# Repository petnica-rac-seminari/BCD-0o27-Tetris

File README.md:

CHECK THE DOCUMENTATION FOLDER FOR INFORMATION ABOUT THE HARDWARE AND HOW TO BUILD IT.

The BalcCon Cyberdeck 0o27 (BCD-0o27) comes with a development framework that makes it easier to add functionality to the cyberdeck. This development guide introduces the framework, advises coding best practices and provides examples for adding functionality to the BCD.
Of course, you can ignore all of that and program the BCD either with esp-idf, rust, or any other framework that allows you to program ESP32 chips directly. However, this is not covered in this guideline.

# Introduction to the BCD-0o27 Framework
Before reading this chapter it is advisable to get  a local copy of the framework (see [[#Getting the Framework]]) and set up the development environment (see [[#Setting up the Development Toolchain]]). 
The framework consists of the following components:
- **Drivers**: The drivers for the hardware, namely the ST7735 display, the WS2812 LEDs  and the input buttons (aka controller) as well as the serial console. (Sometimes, drivers and libraries are not distinguished)
- **Libraries**: Libraries are provided for common tasks like opening a console on the serial port, establishing ssl connections or displaying graphical elements.
- **Modules**: Modules are programs that can be launched by the user. They can be simplest demo applications or complex programs.
- **Console Commands**: Console commands are programs that can be launched from the console. As modules, console commands can have any level of complexity. While usually they mainly interact with the serial console, they may - just as modules - access other hardware as well.

This document is currently being developed. For the time being, it is recommended to check the appendix to clone the repository. Then use the example firmware provided in the directory.

> [!info]
> You can connect to the badge using a serial console and a usb-c data cable. Make sure you use a terminal that understands ansi sequences. You can use the integrated serial monitor of platformio or espressif, but its highly recommended to use syncterm or minicom.

> [!warning]
> There currently is a bug in the serial console that will not give you a prompt when you connect using a serial terminal. In that case, leave the connection open and simply reset the badge by pushing the reset button - left button under the display.

# Appendix
## Getting the Framework
The framework is hosted as a git repository at https://gitlab.com/fschuetz/bcd-0o27.git. The repository makes heavy use of submodules, as many components for the BCD-0o27 are developed in parallel.
To create a local repository using git follow these steps:
```bash
git clone --recurse-submodules https://gitlab.com/fschuetz/bcd-0o27
```

## Setting up the Development Toolchain
In this chapter we will show how to set up the development environment consisting of git, espidf, Microsoft Visual Studio Code and Plattformio. If you are an experienced user, feel free to use the IDE of your choice.
### Installing GIT and cloning the repository
We will use git from the command line, as we have to deal with submodules, which are not well supported in the Visual Studio Code IDE.
If you have git already installed, you can skip this step.
1. Install git for your platform. Follow the guide at [Gitlab](https://docs.gitlab.com/ee/topics/git/how_to_install_git/)
2. Clone the repository: 
    ```bash
    git clone --recurse-submodules https://gitlab.com/fschuetz/bcd-0o27
    ```
Some tips on working with submodules, in case you run into a head detached situation: https://stackoverflow.com/questions/18770545/why-is-my-git-submodule-head-detached-from-master

### Install Microsoft Visual Studio Code (VSCode)
1. Install [VSCode](https://code.visualstudio.com/) for your operating system.
2. Open VSCode.

### Install C/C++ and PlatformIO Extensions
1. In VSCode: Open the "Extensions" side bar on the left side.
2. Search for the "C/C++" extension by Mircrosoft and install it.
3. Search for the PlatformIO IDE by PlatformIO and install it. See [PlatformIO IDE for VSCode](https://docs.platformio.org/en/latest/integration/ide/vscode.html#ide-vscode)
4. Once installation has finished, restart VSCode

### Build and Upload the Firmware 
In this chapter we will build the filesystem image and the firmware and upload both to the badge. If this works, then you can start developing your own firmware using the framework. For testing we highly recommend, taking the example in the directory `firmware/example` rather than the framework, as the example will give you running firmware that allows you to see something actually happening.
1. Start Microsoft Visual Studio and make sure you are in a new window, with no project loaded.
2. Select the alien head in the left bar (Platformio menu)
3. A left band appears. Select the blue button "Pick a folder"
4. From the cloned repository choose the `firmware/example` or the `firmware/framework` folder (as written above, its recommended to start with the example rather than the plain framework).
5. Click open.
6. Wait for platformio to configure itself. This is IMPORTANT: Between now and building the file there might raise popups in the bottom left corner asking you to install extensions or configurations. Usually you are asked to intall C++ specific extensions and CMake specific extensions. Confirm all of them. For CMake, if asked, you can "scan for kits". Scan for kits may also go away on itself, then everything is fine as well. 
7. If all went well so far you will recognise a blue ribbon / button on the bottom and some symbols like a home, a checkmark, roght pointing arrow etc.. If there is the message "Platformio: Loading tasks..." wait until it disapears. (this may take a long while). PlatformIO will automatically configure the project.
8. Open the file main.cpp in the "src" folder.
9. In the bottom task list (with the blue ribbon / button and the checkmark etc...), first choose the build environment by clicking on the symbol that looks like a folder and says "Switch Platformio Project Environment" if you hover over it. Usually it reads default right to the symbol. Choose `env:BCD-0o27-5KY` (or the `env:BCD-0o27-5KY-release` if you want to build for release rather than debug - if unsure make a debug build).
10. Now select the checkmark to build the project. This builds the project. Dependencies are pulled in automatically. In case Platformio does not pull in the Espressif 32 framework, follow the steps in the note below to install it manually.
11. If the project builds successfully, connect your badge to the computer using a usb-c cable (make sure it is actually a data cable and not just a charging cable)
12. Make sure the device is recognised. If the device is not recognised and a com port assigned, you might have to install a driver for the CH340 serial bridge. Follow the instructions from [Sparkfun](https://learn.sparkfun.com/tutorials/how-to-install-ch340-drivers/all#drivers-if-you-need-them)
13. Once the device is recognised, in VSCode we will build the file system image, upload it and then upload the code.
14. From the side bar choose the PlatformIO icon (alien head)
15. Select BCD-0o27 -> Plattform -> Build Filesystem Image
16. When finished, select BCD-0o27 -> Platform -> Upload Filesystem Image (BCD-0o27)
17. When finished, select the right pointing arrow ("Platformio: Upload") in the blue ribbon at the bottom. The project will be built and uploaded to the badge.
18. Either launch the serial console from the blue ribbon by selecting the plug icon ("Platformio: Serial Monitor") or use minicom (preferred). Note, that the Platformio Serial Monitor may display some strange characters or double print the prompt as it does not fully support the output mode. IMPORTANT: Due to a bug, the serial console only works for input if the connection was made at badge startup. If you do not see a prompt, leave the console on and restart the badge by pushing the power button (left between display and battery holder).
19. CRITICAL: Make sure, that you DO NOT have a serial monitor running when trying to flash the badge. This will lead to flash failure (for both, filesystem and firmware).

Note: The Espressif 32 framework should install automatically when building the project. If this is not the case, you can install it manually:
1. Open the Platformio sidebar (left side, alien head icon).
2. Select PIO Home -> Platforms
3. Click on the "Embedded" tab. Search for "Espressif 32" and click it.
4. Install the latest version. (At the time of writing this is version 5.1.0. While we plan to adapt the framework to newer versions, you might want to select this version if the newest version is not working due to breaking changes.)
5. Once the installation has completed confirm the success dialog.
### Helpful Resources
[Espressif 32 for Platformio](https://docs.platformio.org/en/latest/platforms/espressif32.html)

## Misc notes - ignore please
### Updating mirrors 
Go to lib directory of mirror
```
git fetch upstream 
git merge upstream/master
git push
```

### Updating submodules
```
git fetch
git pull
```

# Coding Style
```c++
ESP_LOGE(TAG_MODULE_NAME, "This is a rather long error message."
		"It should be spred on two lines");
```
If functions too long, spread on multiple lines. Two lines, indent second line by one tab and finish the line with closing bracket and ;. If more than two lines use one argument per line and close on a separate line as follows:
```c++
myfunction_with_many_arguments(
	argument 1,
	argument 2,
	argument 3

```

TO BE CONTINUED

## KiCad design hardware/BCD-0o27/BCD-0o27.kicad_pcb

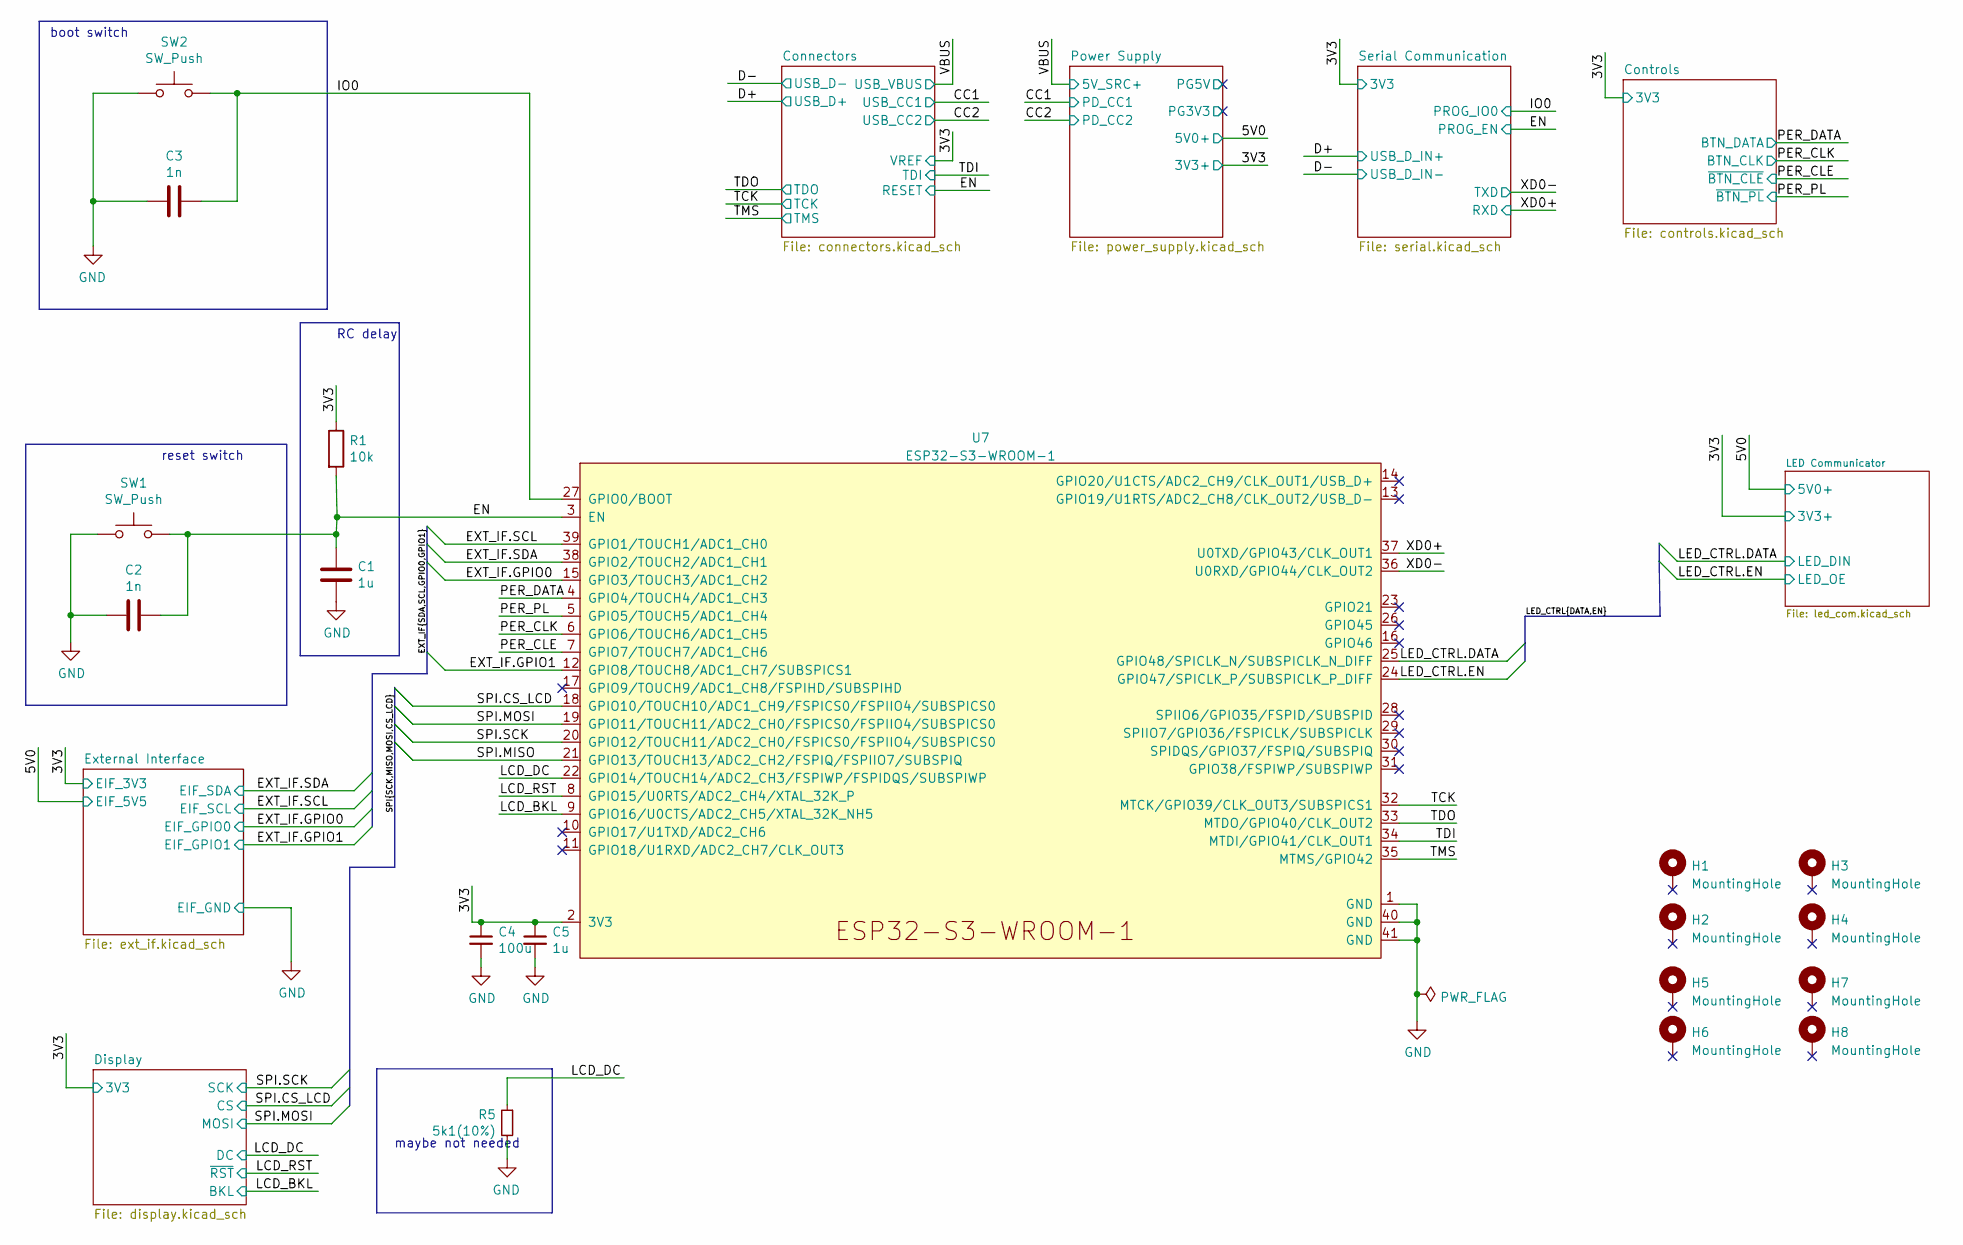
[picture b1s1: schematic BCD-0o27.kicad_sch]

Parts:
C1, C5: 1u; C_0805_2012Metric; LCSC C28323
C2, C3: 1n; C_0805_2012Metric; LCSC C46653
C4: 100u; C_1206_3216Metric; LCSC C15008
H1, H2, H3, H4, H5, H6, H7, H8: MountingHole; MountingHole_2.2mm_M2_ISO7380_Pad_TopBottom
R1: 10k; R_0805_2012Metric; LCSC C17414
R5: 5k1(10%); R_0603_1608Metric; LCSC C23186
SW1, SW2: SW_Push; XUNPU TS-1087S Tactile Switch; LCSC C455268
U7: ESP32-S3-WROOM-1; LCSC C2913202

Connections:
/3V3: C4.1, C5.1, R1.1, U7.2 (3V3); also elsewhere on the board
/EN: C1.1, C2.1, R1.2, SW1.2, U7.3 (EN); also elsewhere on the board
/EXT_IF.GPIO0: U7.15 (GPIO3/TOUCH3/ADC1_CH2); also elsewhere on the board
/EXT_IF.GPIO1: U7.12 (GPIO8/TOUCH8/ADC1_CH7/SUBSPICS1); also elsewhere on the board
/EXT_IF.SCL: U7.39 (GPIO1/TOUCH1/ADC1_CH0); also elsewhere on the board
/EXT_IF.SDA: U7.38 (GPIO2/TOUCH2/ADC1_CH1); also elsewhere on the board
/IO0: C3.1, SW2.1, U7.27 (GPIO0/BOOT); also elsewhere on the board
/LCD_BKL: U7.9 (GPIO16/U0CTS/ADC2_CH5/XTAL_32K_NH5); also elsewhere on the board
/LCD_DC: R5.1, U7.22 (GPIO14/TOUCH14/ADC2_CH3/FSPIWP/FSPIDQS/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); also elsewhere on the board
/LCD_RST: U7.8 (GPIO15/U0RTS/ADC2_CH4/XTAL_32K_P); also elsewhere on the board
/LED_CTRL.DATA: U7.25 (GPIO48/SPICLK_N/SUBSPICLK_N_DIFF); also elsewhere on the board
/LED_CTRL.EN: U7.24 (GPIO47/SPICLK_P/SUBSPICLK_P_DIFF); also elsewhere on the board
/PER_CLE: U7.7 (GPIO7/TOUCH7/ADC1_CH6); also elsewhere on the board
/PER_CLK: U7.6 (GPIO6/TOUCH6/ADC1_CH5); also elsewhere on the board
/PER_DATA: U7.4 (GPIO4/TOUCH4/ADC1_CH3); also elsewhere on the board
/PER_PL: U7.5 (GPIO5/TOUCH5/ADC1_CH4); also elsewhere on the board
/SPI.CS_LCD: U7.18 (GPIO10/TOUCH10/ADC1_CH9/FSPICS0/FSPIIO4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); also elsewhere on the board
/SPI.MISO: U7.21 (GPIO13/TOUCH13/ADC2_CH2/FSPIQ/FSPIIO7/S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)
/SPI.MOSI: U7.19 (GPIO11/TOUCH11/ADC2_CH0/FSPICS0/FSPIIO4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); also elsewhere on the board
/SPI.SCK: U7.20 (GPIO12/TOUCH11/ADC2_CH0/FSPICS0/FSPIIO4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); also elsewhere on the board
/TCK: U7.32 (MTCK/GPIO39/CLK_OUT3/SUBSPICS1); also elsewhere on the board
/TDI: U7.34 (MTDI/GPIO41/CLK_OUT1); also elsewhere on the board
/TDO: U7.33 (MTDO/GPIO40/CLK_OUT2); also elsewhere on the board
/TMS: U7.35 (MTMS/GPIO42); also elsewhere on the board
/XD0+: U7.37 (U0TXD/GPIO43/CLK_OUT1); also elsewhere on the board
/XD0-: U7.36 (U0RXD/GPIO44/CLK_OUT2); also elsewhere on the board
GND: C1.2, C2.2, C3.2, C4.2, C5.2, R5.2, SW1.1, SW2.2, U7.1 (GND), U7.40 (GND), U7.41 (GND); also elsewhere on the board

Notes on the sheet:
RC delay
maybe not needed
reset switch
boot switch

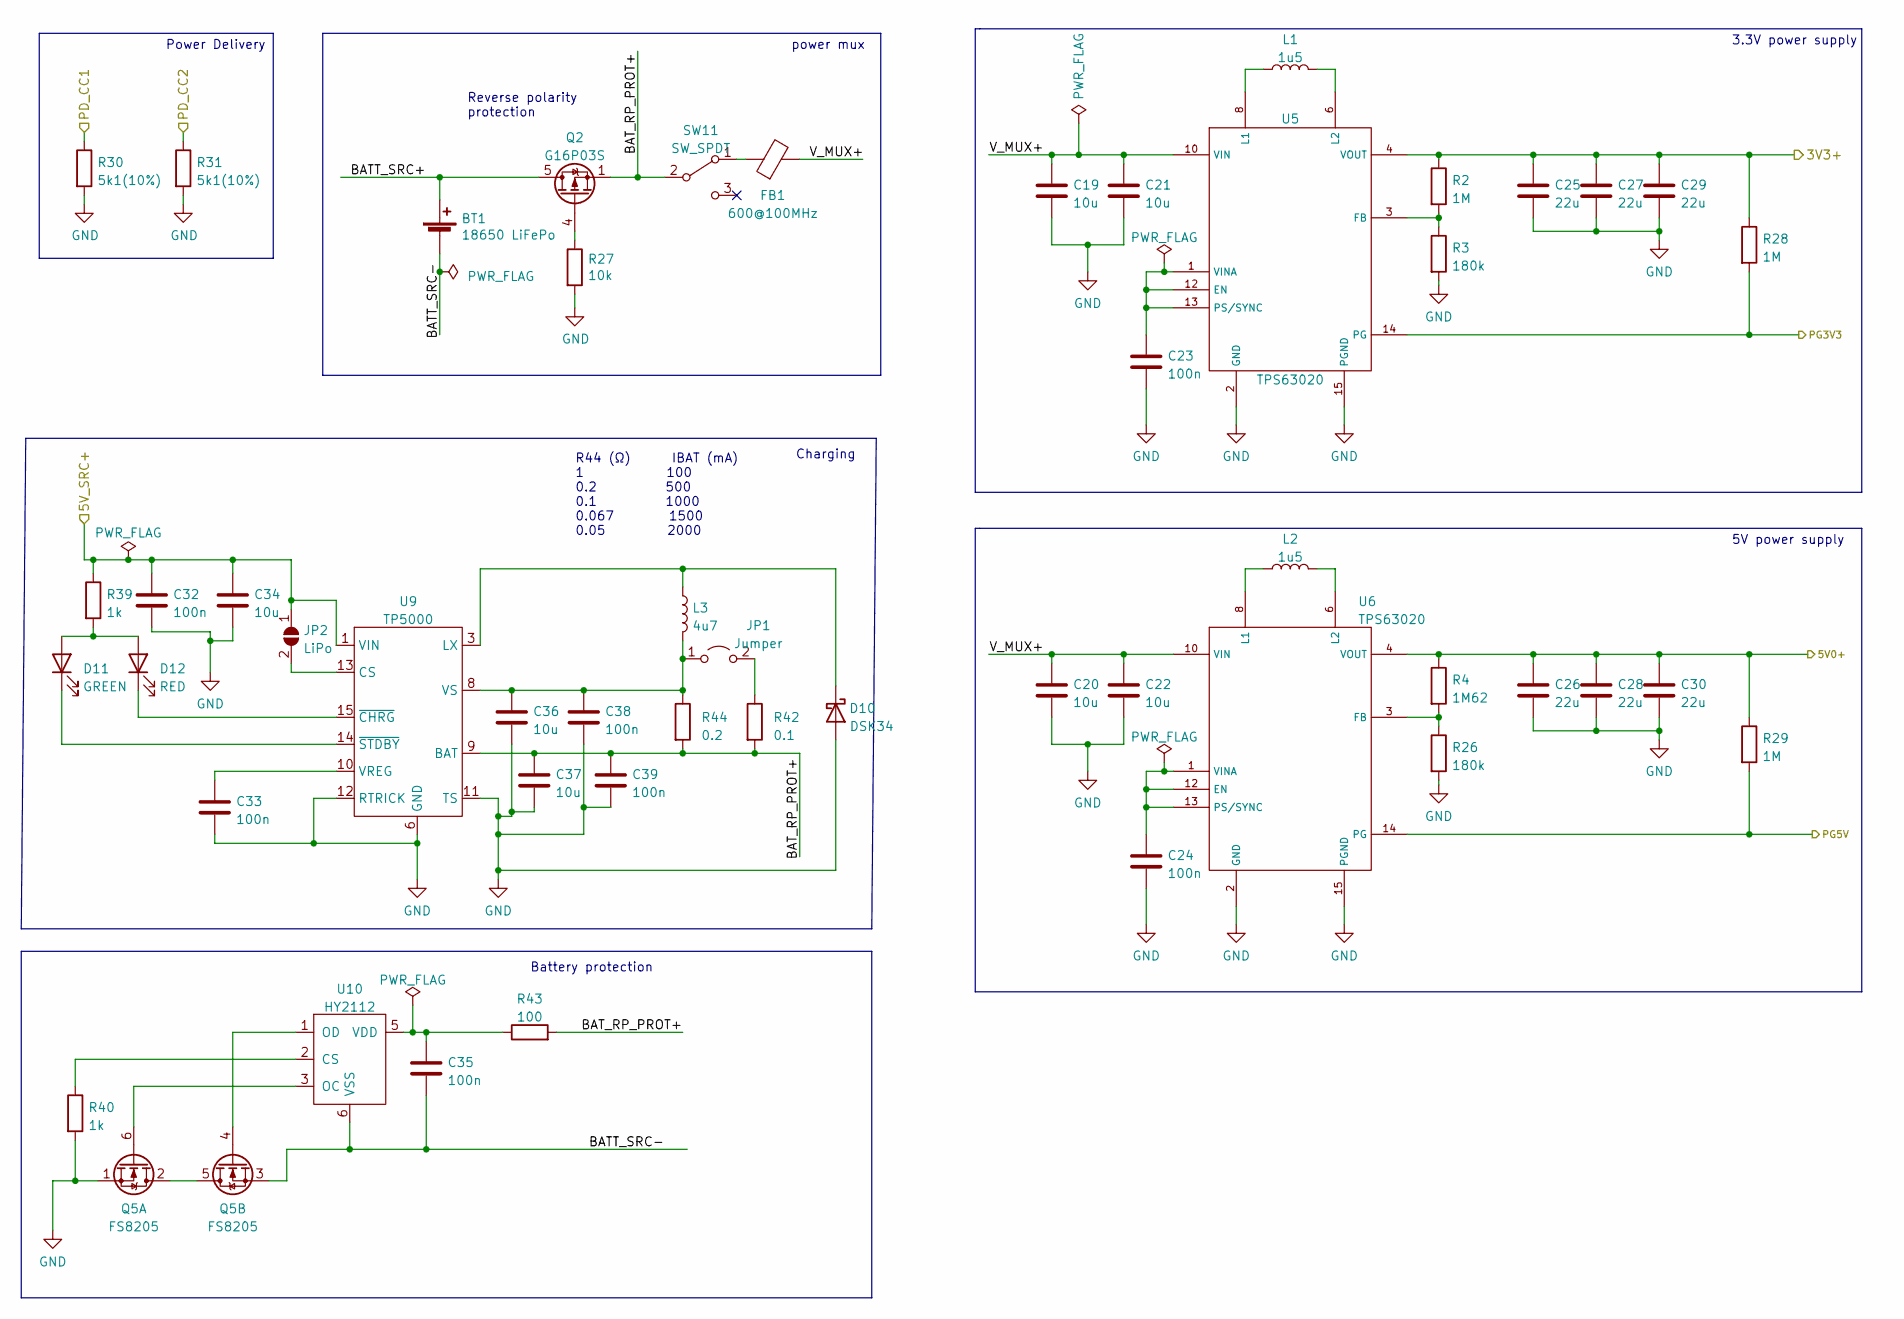
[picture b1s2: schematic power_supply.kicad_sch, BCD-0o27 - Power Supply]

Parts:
BT1: 18650 LiFePo; BatteryHolder_SMD_SMT_1x18650
C19, C20, C21, C22, C34, C36, C37: 10u; C_0603_1608Metric; LCSC C19702
C23, C24, C32, C33, C35, C38, C39: 100n; C_0603_1608Metric; LCSC C14663
C25, C26, C27, C28, C29, C30: 22u; C_0603_1608Metric; LCSC C59461
D10: DSK34; D_SOD-123; LCSC C908230
D11: GREEN; LED_0805_2012Metric; LCSC C2297
D12: RED; LED_0805_2012Metric; LCSC C84256
FB1: 600@100MHz; L_0805_2012Metric; LCSC C1017
JP1: Jumper; Jumper_P2.54mm_D1.2mm; LCSC C5116481
JP2: LiPo; SolderJumper-2_P1.3mm_Open_RoundedPad1.0x1.5mm
L1, L2: 1u5; L_Murata_FDSD0518; LCSC C2931055
L3: 4u7; L_Sunlord_MWSA0503S; LCSC C351098
Q2: G16P03S; SOP-8_3.9x4.9mm_P1.27mm; LCSC C840046
Q5: FS8205; TSOT-23-6; LCSC C908265
R2, R28, R29: 1M; R_0603_1608Metric; LCSC C22935
R3, R26: 180k; R_0603_1608Metric; LCSC C22827
R4: 1M62; R_0603_1608Metric; LCSC C407540
R27: 10k; R_0805_2012Metric; LCSC C17414
R30, R31: 5k1(10%); R_0603_1608Metric; LCSC C23186
R39, R40: 1k; R_0603_1608Metric; LCSC C21190
R42: 0.1; R_0603_1608Metric; LCSC C5120068
R43: 100; R_0805_2012Metric; LCSC C17408
R44: 0.2; R_0603_1608Metric; LCSC C79773
SW11: SW_SPDT; SS-12M11G3; LCSC C2879832
U5, U6: TPS63020; QFN14-3X4MM; LCSC C15483
U9: TP5000; QFN-16-1EP_4x4mm_P0.65mm_EP2.1x2.1mm; LCSC C51699
U10: HY2112; TSOT-23-6; LCSC C161942

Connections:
/3V3: C25.1, C27.1, C29.1, R2.1, R28.1, U5.4 (VOUT), U5.5 (VOUT); also elsewhere on the board
/5V0: C26.1, C28.1, C30.1, R4.1, R29.1, U6.4 (VOUT), U6.5 (VOUT); also elsewhere on the board
/CC1: R30.1; also elsewhere on the board
/CC2: R31.1; also elsewhere on the board
/Power Supply/BATT_SRC+: BT1.1 (+), Q2.5 (D), Q2.6 (D), Q2.7 (D), Q2.8 (D)
/Power Supply/BATT_SRC-: BT1.2 (-), C35.2, Q5.3 (S2), U10.6 (VSS)
/Power Supply/BAT_RP_PROT+: C37.1, C39.1, Q2.1 (S), Q2.2 (S), Q2.3 (S), R42.2, R43.2, R44.2, SW11.2 (B), U9.9 (BAT)
/Power Supply/PG3V3: R28.2, U5.14 (PG)
/Power Supply/PG5V: R29.2, U6.14 (PG)
/Power Supply/V_MUX+: C19.1, C20.1, C21.1, C22.1, FB1.2, U5.10 (VIN), U5.11 (VIN), U6.10 (VIN), U6.11 (VIN)
/VBUS: C32.1, C34.1, JP2.1 (A), R39.1, U9.1 (VIN), U9.2 (VIN), U9.16 (VIN); also elsewhere on the board
GND: C19.2, C20.2, C21.2, C22.2, C23.2, C24.2, C25.2, C26.2, C27.2, C28.2, C29.2, C30.2, C32.2, C33.2, C34.2, C36.2, C37.2, C38.2, C39.2, D10.2 (A), Q5.1 (S2), R3.2, R26.2, R27.2, R30.2, R31.2, R40.2, U5.2 (GND), U5.15 (PGND), U5.16 (PGND), U5.17 (PGND), U5.18 (PGND), U5.19 (PGND), U5.20 (PGND), U5.21 (PGND), U5.22 (PGND), U5.23 (PGND), U6.2 (GND), U6.15 (PGND), U6.16 (PGND), U6.17 (PGND), U6.18 (PGND), U6.19 (PGND), U6.20 (PGND), U6.21 (PGND), U6.22 (PGND), U6.23 (PGND), U9.6 (GND), U9.7 (GND), U9.11 (TS), U9.12 (RTRICK); also elsewhere on the board
unnamed: C23.1, U5.1 (VINA), U5.12 (EN), U5.13 (PS/SYNC)
unnamed: C24.1, U6.1 (VINA), U6.12 (EN), U6.13 (PS/SYNC)
unnamed: C35.1, R43.1, U10.5 (VDD)
unnamed: D10.1 (K), L3.1, U9.3 (LX), U9.4 (LX), U9.5 (LX)
unnamed: D11.2 (A), D12.2 (A), R39.2
unnamed: D11.1 (K), U9.14 (~STDBY)
unnamed: D12.1 (K), U9.15 (~CHRG)
unnamed: C36.1, C38.1, JP1.1 (A), L3.2, R44.1, U9.8 (VS)
unnamed: JP1.2 (B), R42.1
unnamed: JP2.2 (B), U9.13 (CS)
unnamed: L1.1, U5.8 (L1), U5.9 (L1)
unnamed: L1.2, U5.6 (L2), U5.7 (L2)
unnamed: L2.1, U6.8 (L1), U6.9 (L1)
unnamed: L2.2, U6.6 (L2), U6.7 (L2)
unnamed: Q2.4 (G), R27.1
unnamed: Q5.2 (D12), Q5.5 (D12)
unnamed: Q5.6 (G2), U10.3 (OC)
unnamed: Q5.4 (G2), U10.1 (OD)
unnamed: FB1.1, SW11.1 (A)
unnamed: R2.2, R3.1, U5.3 (FB)
unnamed: R4.2, R26.1, U6.3 (FB)
unnamed: C33.1, U9.10 (VREG)
unnamed: R40.1, U10.2 (CS)

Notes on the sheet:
3.3V power supply
Power Delivery
power mux
Charging
5V power supply
Battery protection
Reverse polarity protection
R44 (Ω) IBAT (mA) 1 100 0.2 500 0.1 1000 0.067 1500 0.05 2000

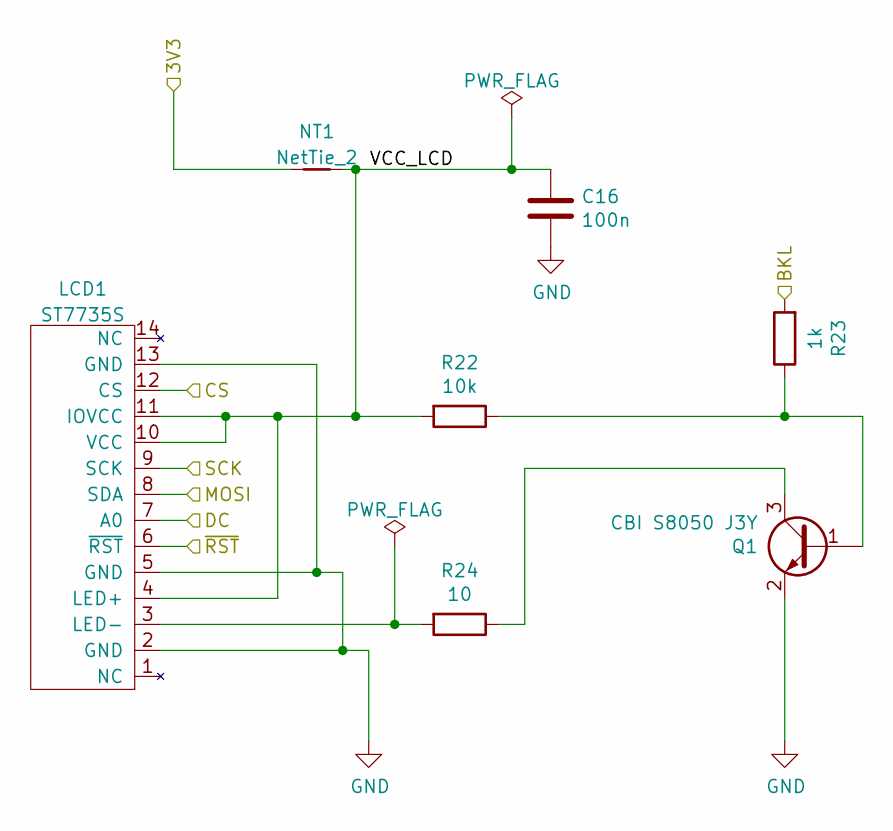
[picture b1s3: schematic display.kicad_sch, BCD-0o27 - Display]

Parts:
C16: 100n; C_0603_1608Metric; LCSC C14663
LCD1: ST7735S; ST7735S-1.8-Inch-128x160px-tft
NT1: NetTie_2; NetTie-2_SMD_Pad0.5mm
Q1: CBI S8050 J3Y; SOT-23; LCSC C2146
R22: 10k; R_0805_2012Metric; LCSC C17414
R23: 1k; R_0603_1608Metric; LCSC C21190
R24: 10; R_0805_2012Metric; LCSC C17415

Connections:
/3V3: NT1.1; also elsewhere on the board
/Display/VCC_LCD: C16.1, LCD1.4 (LED+), LCD1.10 (VCC), LCD1.11 (IOVCC), NT1.2, R22.2
/LCD_BKL: R23.2; also elsewhere on the board
/LCD_DC: LCD1.7 (A0); also elsewhere on the board
/LCD_RST: LCD1.6 (~RST); also elsewhere on the board
/SPI.CS_LCD: LCD1.12 (CS); also elsewhere on the board
/SPI.MOSI: LCD1.8 (SDA); also elsewhere on the board
/SPI.SCK: LCD1.9 (SCK); also elsewhere on the board
GND: C16.2, LCD1.2 (GND), LCD1.5 (GND), LCD1.13 (GND), Q1.2 (E); also elsewhere on the board
unnamed: LCD1.3 (LED-), R24.2
unnamed: Q1.1 (B), R22.1, R23.1
unnamed: Q1.3 (C), R24.1

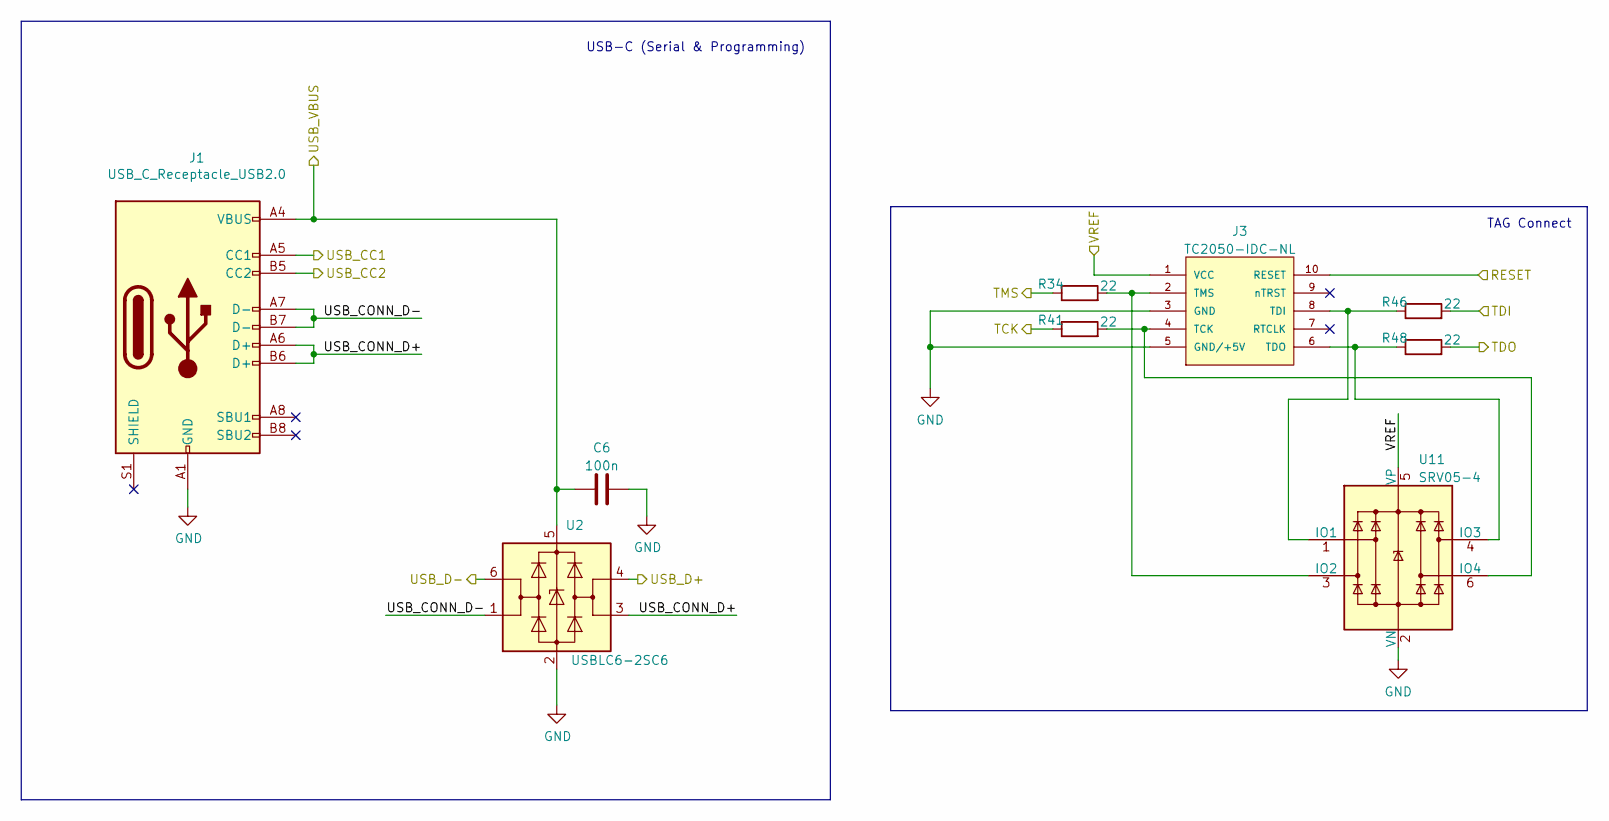
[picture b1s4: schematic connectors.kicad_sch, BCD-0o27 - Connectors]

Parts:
C6: 100n; C_0603_1608Metric; LCSC C14663
J1: USB_C_Receptacle_USB2.0; USB_C_Receptacle_HRO_TYPE-C-31-M-12; LCSC C165948
J3: TC2050-IDC-NL; TAG-CONNECT_TC2050-IDC-NL; PARTREV A
R34, R41, R46, R48: 22; R_0603_1608Metric; LCSC C23345
U2: USBLC6-2SC6; SOT-23-6; LCSC C2687116
U11: SRV05-4; SOT-23-6; LCSC C558418

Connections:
/3V3: J3.1 (VCC), U11.5 (VP); also elsewhere on the board
/CC1: J1.A5 (CC1); also elsewhere on the board
/CC2: J1.B5 (CC2); also elsewhere on the board
/Connectors/USB_CONN_D+: J1.A6 (D+), J1.B6 (D+), U2.3 (I/O2)
/Connectors/USB_CONN_D-: J1.A7 (D-), J1.B7 (D-), U2.1 (I/O1)
/D+: U2.4 (I/O2); also elsewhere on the board
/D-: U2.6 (I/O1); also elsewhere on the board
/EN: J3.10 (RESET); also elsewhere on the board
/TCK: R41.1; also elsewhere on the board
/TDI: R46.2; also elsewhere on the board
/TDO: R48.2; also elsewhere on the board
/TMS: R34.1; also elsewhere on the board
/VBUS: C6.1, J1.A4 (VBUS), J1.A9 (VBUS), J1.B4 (VBUS), J1.B9 (VBUS), U2.5 (VBUS); also elsewhere on the board
GND: C6.2, J1.A1 (GND), J1.A12 (GND), J1.B1 (GND), J1.B12 (GND), J3.3 (GND), J3.5 (GND/+5V), U2.2 (GND), U11.2 (VN); also elsewhere on the board
unnamed: J3.4 (TCK), R41.2, U11.6 (IO4)
unnamed: J3.8 (TDI), R46.1, U11.1 (IO1)
unnamed: J3.6 (TDO), R48.1, U11.4 (IO3)
unnamed: J3.2 (TMS), R34.2, U11.3 (IO2)

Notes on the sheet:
TAG Connect
USB-C (Serial & Programming)

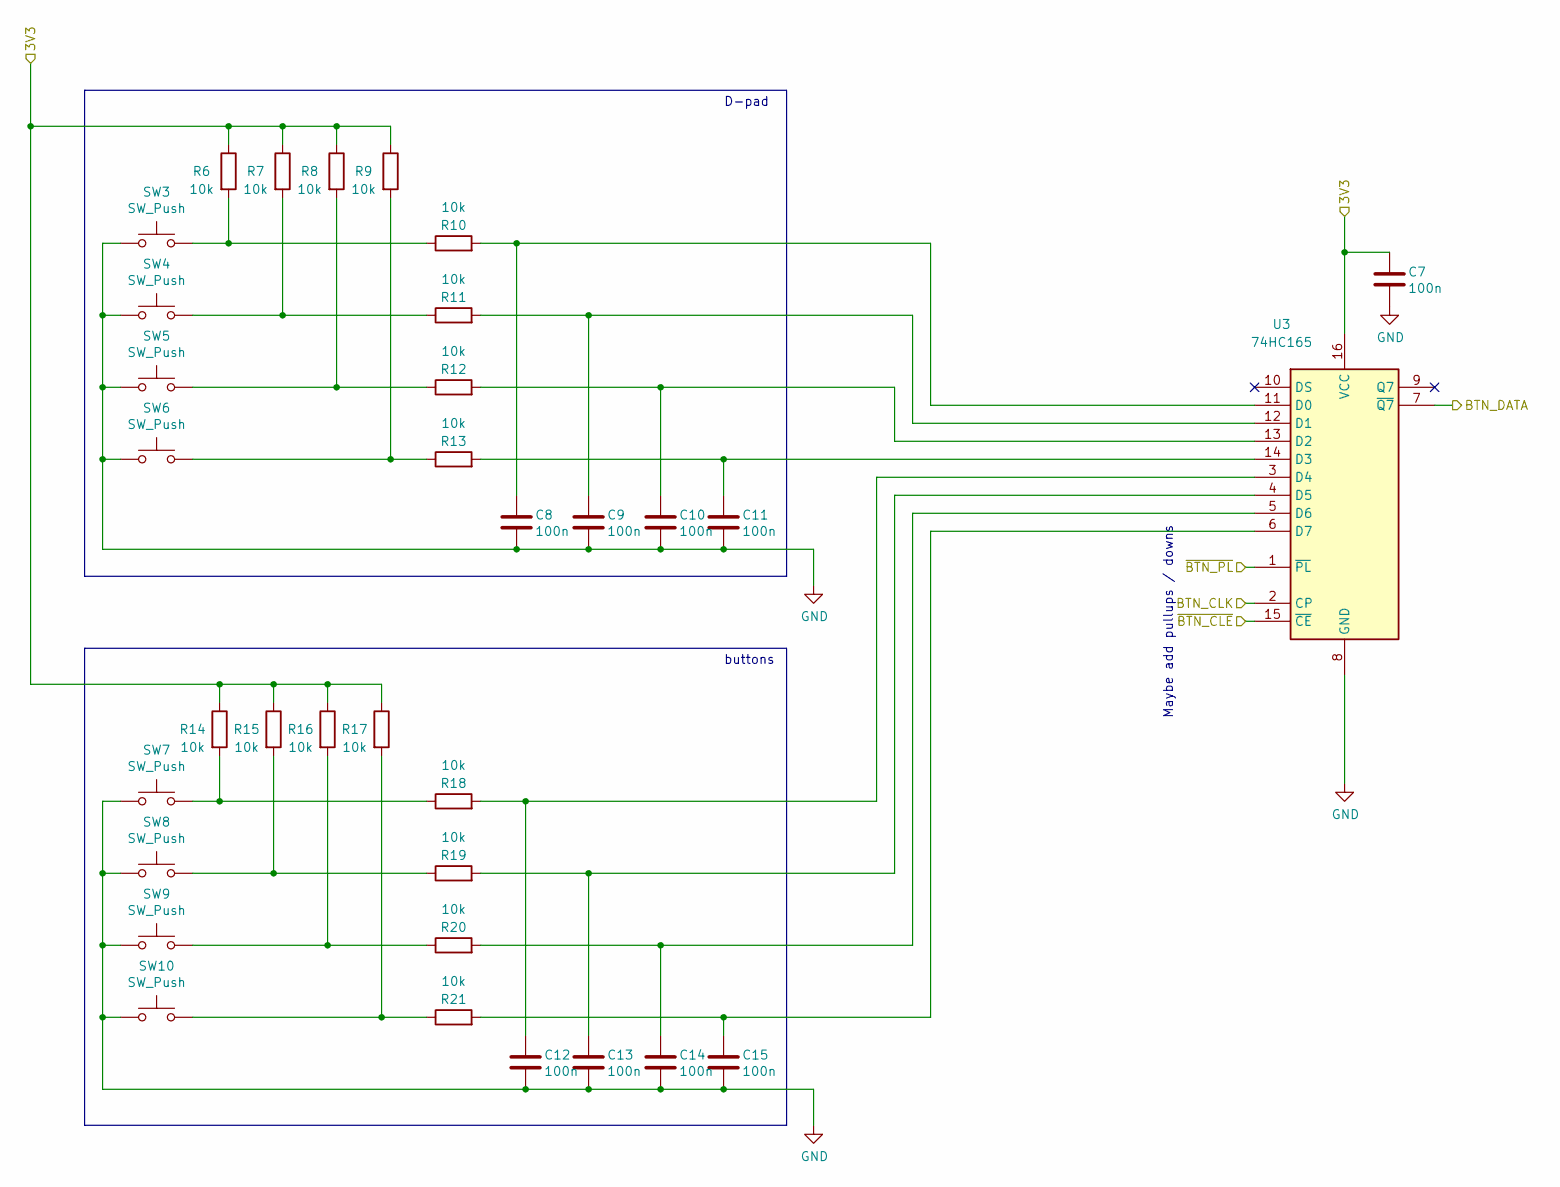
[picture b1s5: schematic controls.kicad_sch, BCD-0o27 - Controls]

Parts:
C7, C8, C9, C10, C11, C12, C13, C14, C15: 100n; C_0603_1608Metric; LCSC C14663
R6, R7, R8, R9, R10, R11, R12, R13, R14, R15, R16, R17, R18, R19, R20, R21: 10k; R_0805_2012Metric; LCSC C17414
SW3, SW4, SW5, SW6, SW7, SW8, SW9, SW10: SW_Push; XUNPU TS-1087S Tactile Switch; LCSC C455268
U3: 74HC165; SOIC-16_3.9x9.9mm_P1.27mm; LCSC C470977

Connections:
/3V3: C7.1, R6.1, R7.1, R8.1, R9.1, R14.1, R15.1, R16.1, R17.1, U3.16 (VCC); also elsewhere on the board
/PER_CLE: U3.15 (~CE); also elsewhere on the board
/PER_CLK: U3.2 (CP); also elsewhere on the board
/PER_DATA: U3.7 (~Q7); also elsewhere on the board
/PER_PL: U3.1 (~PL); also elsewhere on the board
GND: C7.2, C8.2, C9.2, C10.2, C11.2, C12.2, C13.2, C14.2, C15.2, SW3.1, SW4.1, SW5.1, SW6.1, SW7.1, SW8.1, SW9.1, SW10.1, U3.8 (GND); also elsewhere on the board
unnamed: R6.2, R10.1, SW3.2
unnamed: R7.2, R11.1, SW4.2
unnamed: R8.2, R12.1, SW5.2
unnamed: R9.2, R13.1, SW6.2
unnamed: R14.2, R18.1, SW7.2
unnamed: R15.2, R19.1, SW8.2
unnamed: R16.2, R20.1, SW9.2
unnamed: R17.2, R21.1, SW10.2
unnamed: C8.1, R10.2, U3.11 (D0)
unnamed: C9.1, R11.2, U3.12 (D1)
unnamed: C10.1, R12.2, U3.13 (D2)
unnamed: C11.1, R13.2, U3.14 (D3)
unnamed: C12.1, R18.2, U3.3 (D4)
unnamed: C13.1, R19.2, U3.4 (D5)
unnamed: C14.1, R20.2, U3.5 (D6)
unnamed: C15.1, R21.2, U3.6 (D7)

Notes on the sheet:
Maybe add pullups / downs
D-pad
buttons

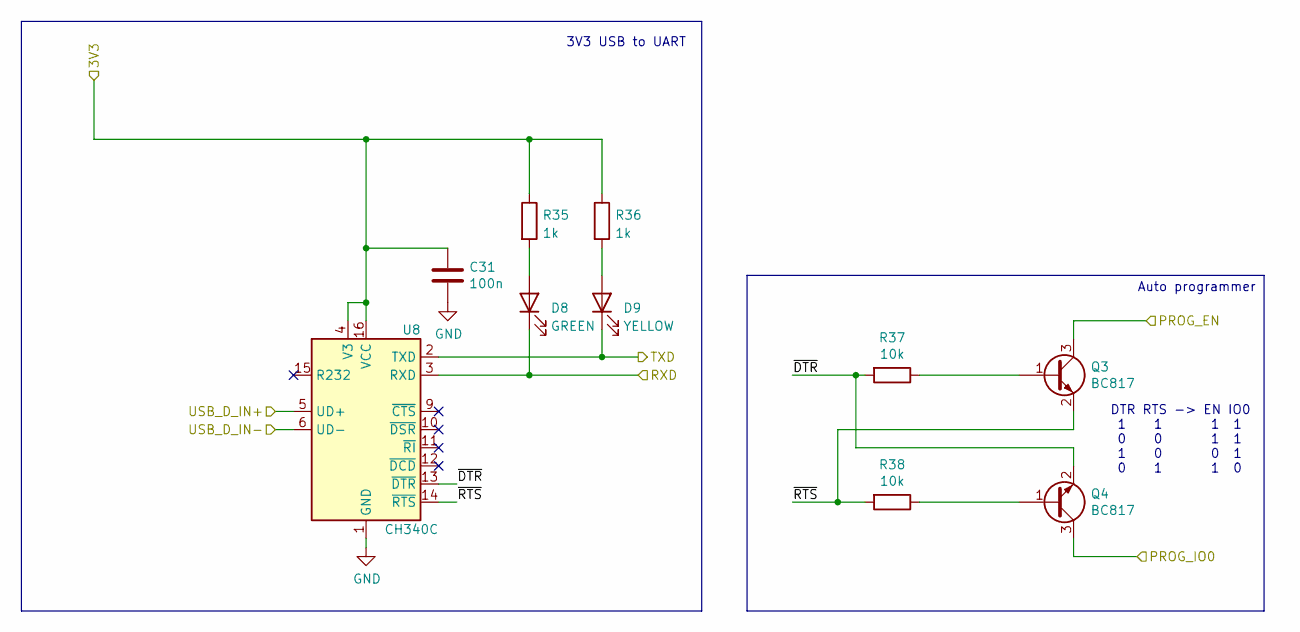
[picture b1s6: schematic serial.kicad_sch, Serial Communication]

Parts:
C31: 100n; C_0603_1608Metric; LCSC C14663
D8: GREEN; LED_0805_2012Metric; LCSC C2297
D9: YELLOW; LED_0805_2012Metric; LCSC C2296
Q3, Q4: BC817; SOT-23; LCSC C475629
R35, R36: 1k; R_0603_1608Metric; LCSC C21190
R37, R38: 10k; R_0805_2012Metric; LCSC C17414
U8: CH340C; SOIC-16_3.9x9.9mm_P1.27mm; LCSC C84681

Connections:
/3V3: C31.1, R35.1, R36.1, U8.4 (V3), U8.16 (VCC); also elsewhere on the board
/D+: U8.5 (UD+); also elsewhere on the board
/D-: U8.6 (UD-); also elsewhere on the board
/EN: Q3.3 (C); also elsewhere on the board
/IO0: Q4.3 (C); also elsewhere on the board
/Serial Communication/~DTR: Q4.2 (E), R37.2, U8.13 (~DTR)
/Serial Communication/~RTS: Q3.2 (E), R38.2, U8.14 (~RTS)
/XD0+: D8.1 (K), U8.3 (RXD); also elsewhere on the board
/XD0-: D9.1 (K), U8.2 (TXD); also elsewhere on the board
GND: C31.2, U8.1 (GND); also elsewhere on the board
unnamed: D8.2 (A), R35.2
unnamed: D9.2 (A), R36.2
unnamed: Q3.1 (B), R37.1
unnamed: Q4.1 (B), R38.1

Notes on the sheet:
Auto programmer
3V3 USB to UART
DTR RTS -> EN IO0 1 1 1 1 0 0 1 1 1 0 0 1 0 1 1 0

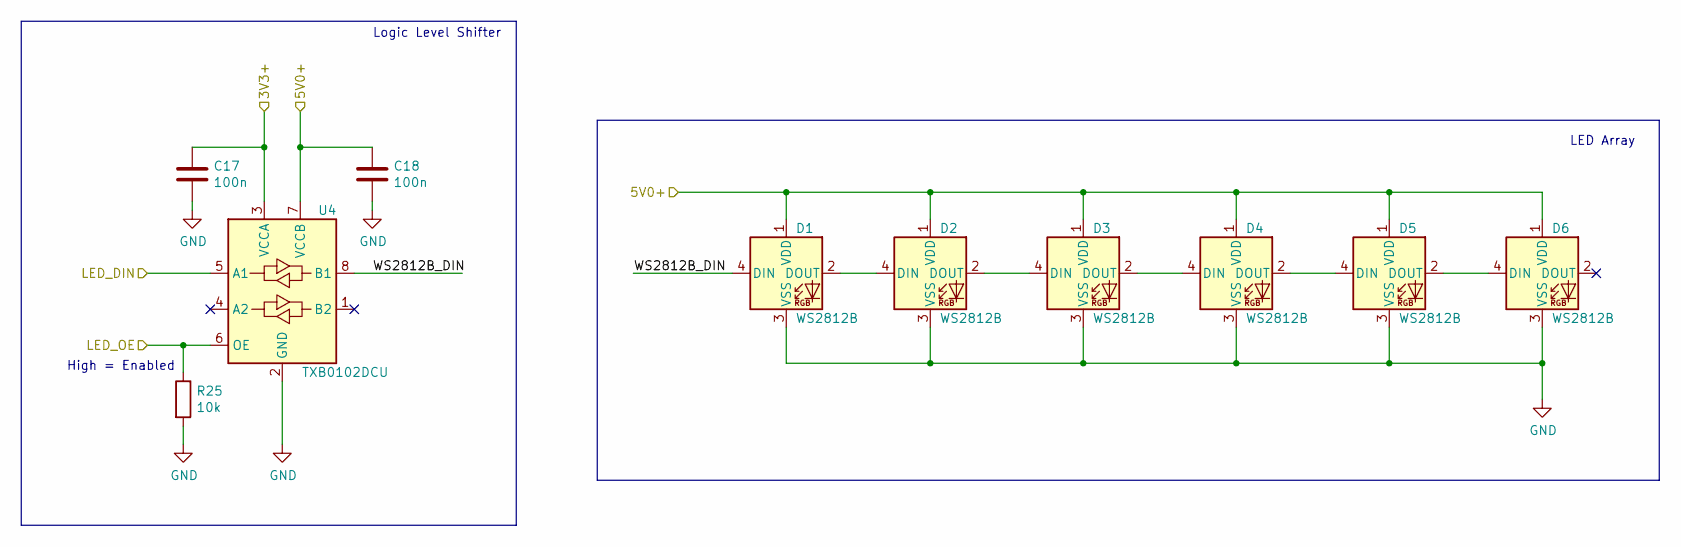
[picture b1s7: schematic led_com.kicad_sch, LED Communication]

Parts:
C17, C18: 100n; C_0603_1608Metric; LCSC C14663
D1, D2, D3, D4, D5, D6: WS2812B; LED_WS2812B_PLCC4_5.0x5.0mm_P3.2mm; LCSC C2761795
R25: 10k; R_0805_2012Metric; LCSC C17414
U4: TXB0102DCU; VSSOP-8_2.4x2.1mm_P0.5mm; LCSC C60709

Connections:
/3V3: C17.1, U4.3 (VCCA); also elsewhere on the board
/5V0: C18.1, D1.1 (VDD), D2.1 (VDD), D3.1 (VDD), D4.1 (VDD), D5.1 (VDD), D6.1 (VDD), U4.7 (VCCB); also elsewhere on the board
/LED Communicator/WS2812B_DIN: D1.4 (DIN), U4.8 (B1)
/LED_CTRL.DATA: U4.5 (A1); also elsewhere on the board
/LED_CTRL.EN: R25.1, U4.6 (OE); also elsewhere on the board
GND: C17.2, C18.2, D1.3 (VSS), D2.3 (VSS), D3.3 (VSS), D4.3 (VSS), D5.3 (VSS), D6.3 (VSS), R25.2, U4.2 (GND); also elsewhere on the board
unnamed: D1.2 (DOUT), D2.4 (DIN)
unnamed: D2.2 (DOUT), D3.4 (DIN)
unnamed: D3.2 (DOUT), D4.4 (DIN)
unnamed: D4.2 (DOUT), D5.4 (DIN)
unnamed: D5.2 (DOUT), D6.4 (DIN)

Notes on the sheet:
High = Enabled
LED Array
Logic Level Shifter

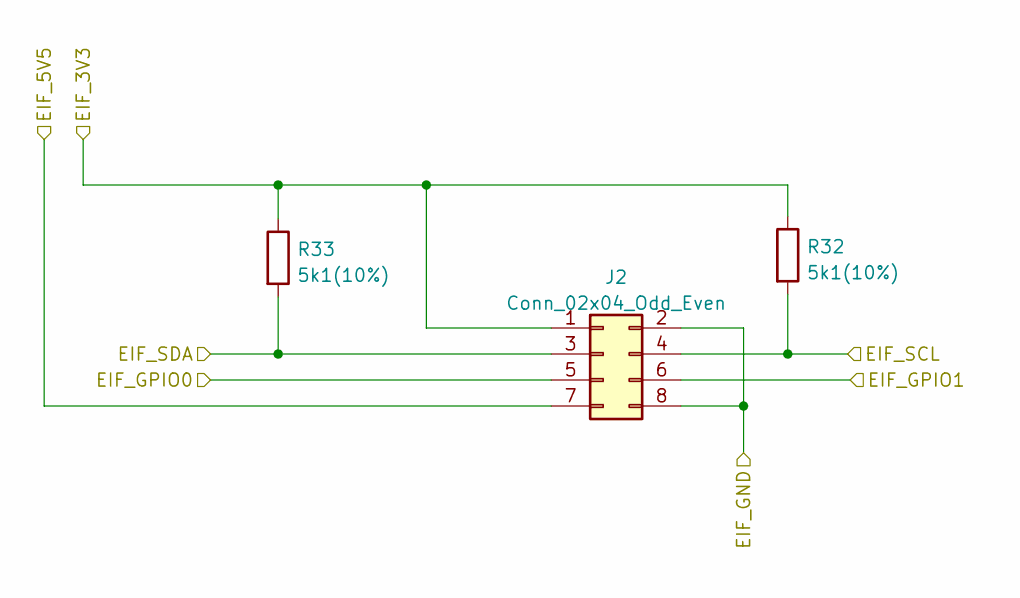
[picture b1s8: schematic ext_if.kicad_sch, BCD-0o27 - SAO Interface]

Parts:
J2: Conn_02x04_Odd_Even; PinSocket_2x04_P2.54mm_Vertical; LCSC C2977588
R32, R33: 5k1(10%); R_0603_1608Metric; LCSC C23186

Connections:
/3V3: J2.1, R32.1, R33.1; also elsewhere on the board
/5V0: J2.7; also elsewhere on the board
/EXT_IF.GPIO0: J2.5; also elsewhere on the board
/EXT_IF.GPIO1: J2.6; also elsewhere on the board
/EXT_IF.SCL: J2.4, R32.2; also elsewhere on the board
/EXT_IF.SDA: J2.3, R33.2; also elsewhere on the board
GND: J2.2, J2.8; also elsewhere on the board

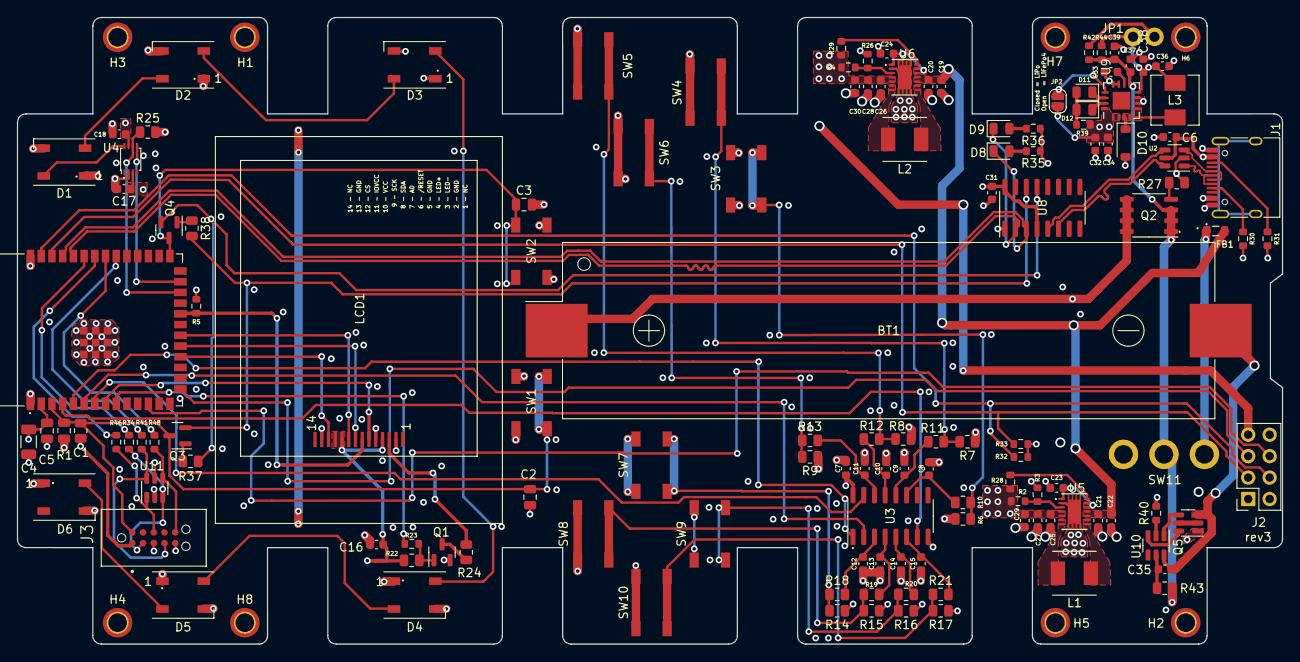
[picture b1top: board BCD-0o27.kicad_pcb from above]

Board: 4 copper layers, 149.9 x 74.2 mm, 142 parts (0 on the bottom side), 99 nets.
